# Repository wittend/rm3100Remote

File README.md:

# rm3100Remote
OSHW (TAPR License) remote magnetometer support board design

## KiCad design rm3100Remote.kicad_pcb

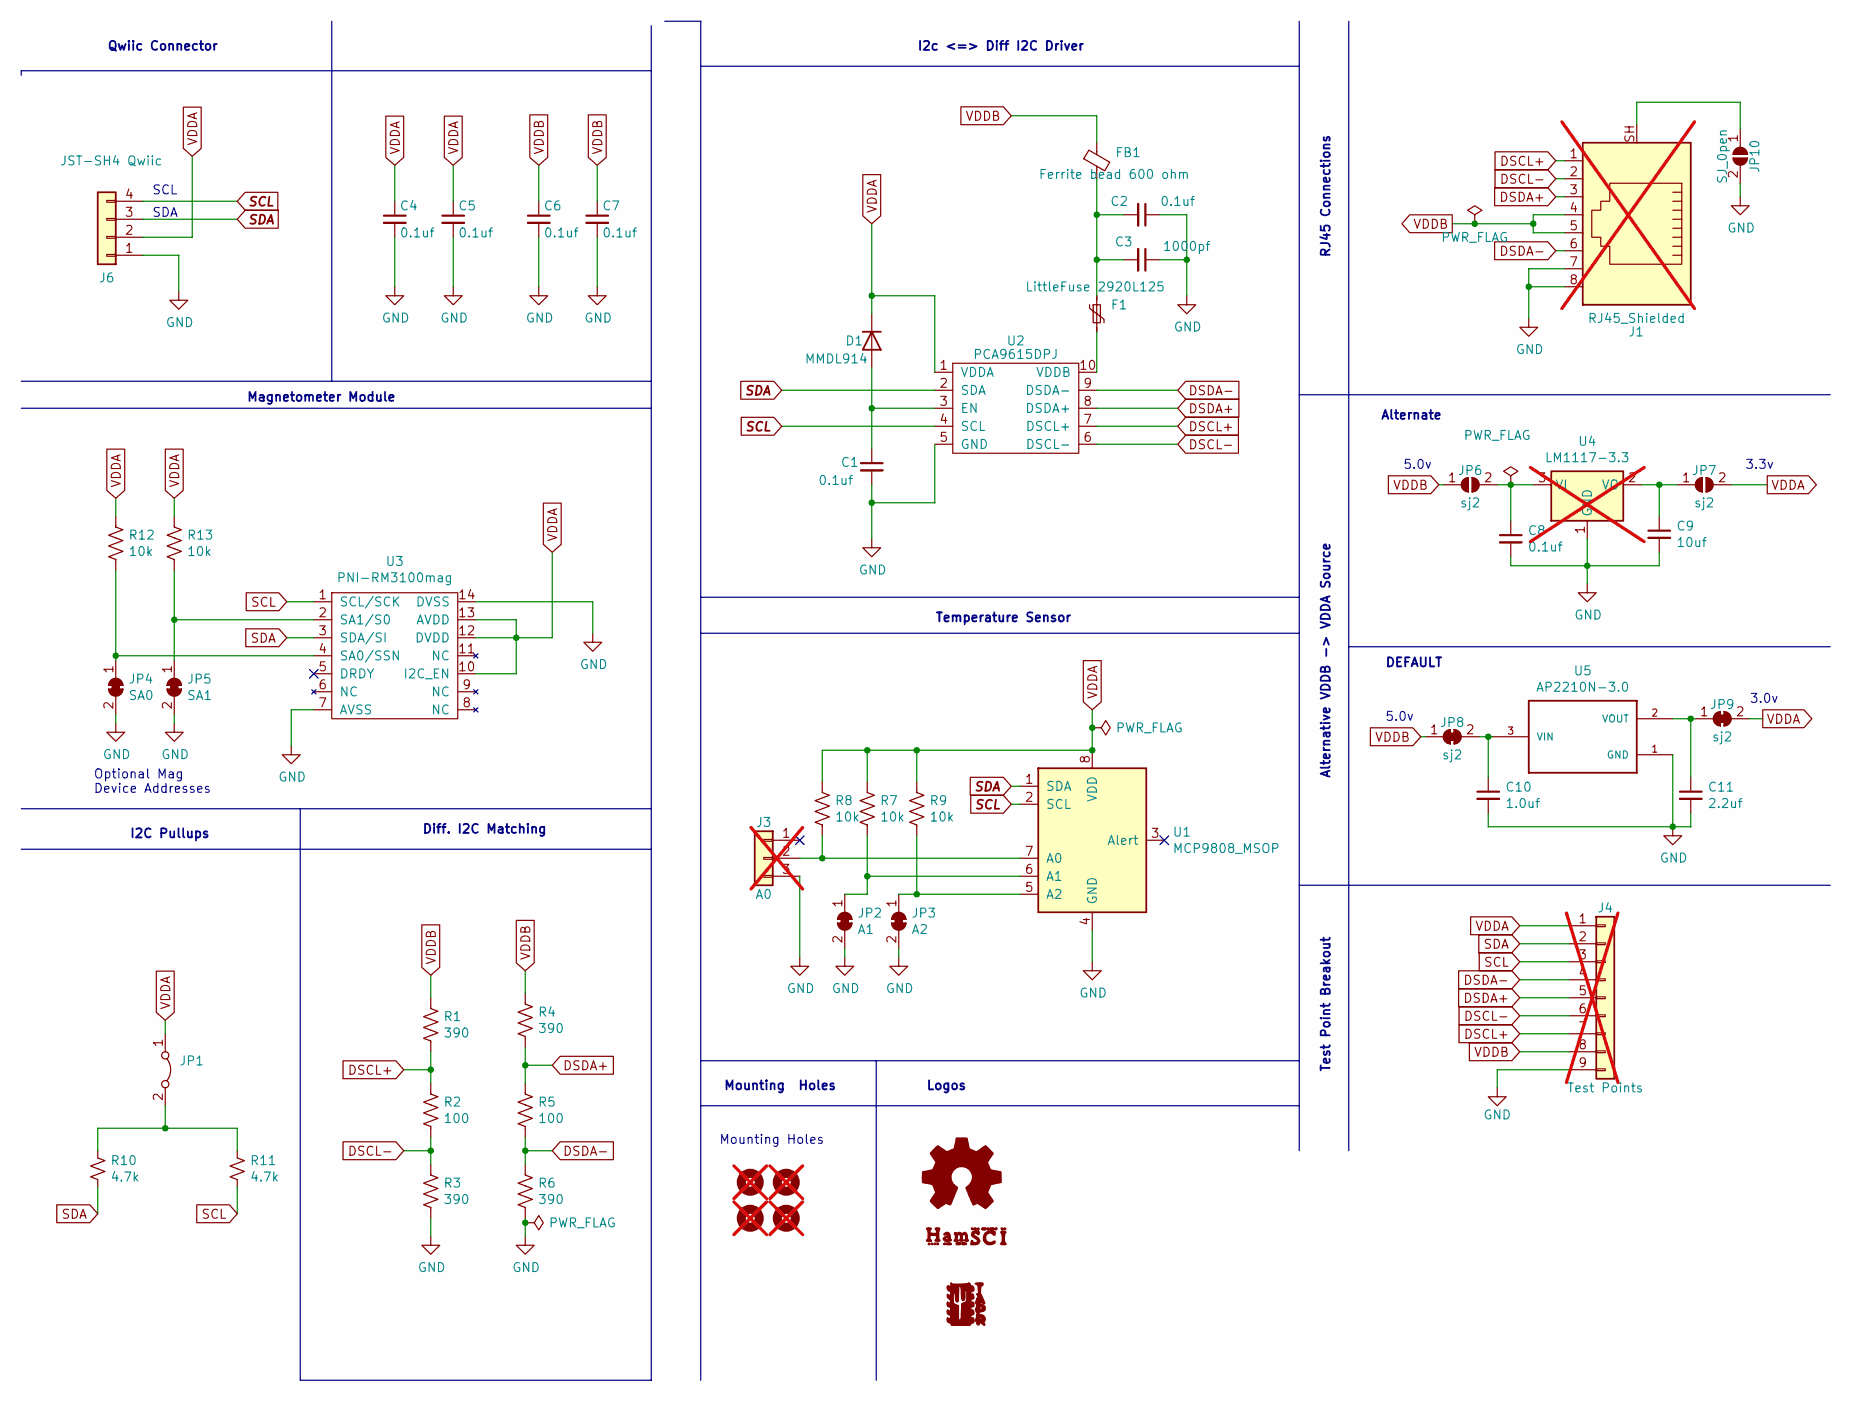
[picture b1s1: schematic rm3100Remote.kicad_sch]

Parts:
C1, C2, C4, C5, C6, C7, C8: 0.1uf; C_0603_1608Metric; LCSC C913909
C3: 1000pf; C_0603_1608Metric
C9: 10uf; C_0603_1608Metric; LCSC C182375
C10: 1.0uf; C_0603_1608Metric; LCSC C525329
C11: 2.2uf; C_0603_1608Metric; LCSC C2835569
D1: MMDL914; D_SOD-523; LCSC C2910101
F1: LittleFuse 2920L125; Fuse_0805_2012Metric; LCSC C192524
FB1: Ferrite bead 600 ohm; 0603; LCSC C79865
J1: RJ45_Shielded; RJ45_Amphenol_RJHSE5380; not fitted
J3: A0; PinHeader_1x03_P2.54mm_Vertical; not fitted
J4: Test Points; PinHeader_1x09_P2.54mm_Vertical; not fitted
J6: JST-SH4 Qwiic; JST_SH_SM04B-SRSS-TB_1x04-1MP_P1.00mm_Horizontal; LCSC C5223639
JP1: Jumper_2_Bridged; SolderJumper-2_P1.3mm_Bridged_RoundedPad1.0x1.5mm
JP2: A1; SolderJumper-2_P1.3mm_Bridged_RoundedPad1.0x1.5mm
JP3: A2; SolderJumper-2_P1.3mm_Bridged_RoundedPad1.0x1.5mm
JP4: SA0; SolderJumper-2_P1.3mm_Bridged_RoundedPad1.0x1.5mm
JP5: SA1; SolderJumper-2_P1.3mm_Bridged_RoundedPad1.0x1.5mm
JP6, JP7: sj2; SolderJumper-2_P1.3mm_Open_RoundedPad1.0x1.5mm
JP8, JP9: sj2; SolderJumper-2_P1.3mm_Bridged_RoundedPad1.0x1.5mm
JP10: SJ_0pen; SolderJumper-2_P1.3mm_Open_RoundedPad1.0x1.5mm
MK1, MK2, MK3, MK4: M2.5; MountingHole_2.7mm_M2.5; not fitted
R1, R3, R4, R6: 390; R_0603_1608Metric; LCSC C2907159
R2, R5: 100; R_0603_1608Metric; LCSC C2838670
R7, R8, R9, R12, R13: 10k; R_0603_1608Metric; LCSC C25804
R10, R11: 4.7k; R_0603_1608Metric; LCSC C304485
U1: MCP9808_MSOP; MSOP-8_3x3mm_P0.65mm; LCSC C94847
U2: PCA9615DPJ; TSSOP-10_3x3mm_P0.5mm; LCSC C2652385
U3: PNI-RM3100mag; PinSocket_PNI_RM3100
U4: LM1117-3.3; SOT-223-3_TabPin2; not fitted
U5: AP2210N-3.0; SOT95P280X145-3N; LCSC C500771

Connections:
DSCL+: J1.1, J4.7, R1.2, R2.1, U2.7 (DSCL+)
DSCL-: J1.2, J4.6, R2.2, R3.1, U2.6 (DSCL-)
DSDA+: J1.3, J4.5, R4.2, R5.1, U2.8 (DSDA+)
DSDA-: J1.6, J4.4, R5.2, R6.1, U2.9 (DSDA-)
GND: C1.2, C2.1, C3.1, C4.2, C5.2, C6.2, C7.2, C8.2, C9.2, C10.2, C11.2, J1.7, J1.8, J3.3, J4.9, J6.1, JP2.2 (B), JP3.2 (B), JP4.2 (B), JP5.2 (B), JP10.2 (B), R3.2, R6.2, U1.4 (GND), U2.5 (GND), U3.7 (AVSS), U3.14 (DVSS), U4.1 (GND), U5.1 (GND)
unnamed: C2.2, C3.2, F1.1, FB1.2
unnamed: C1.1, D1.2 (A), U2.3 (EN)
unnamed: J3.2, R8.2, U1.7 (A0)
unnamed: JP1.2 (B), R10.1, R11.1
unnamed: JP2.1 (A), R7.2, U1.6 (A1)
unnamed: JP3.1 (A), R9.2, U1.5 (A2)
unnamed: JP4.1 (A), R12.2, U3.4 (SA0/SSN)
unnamed: JP5.1 (A), R13.2, U3.2 (SA1/S0)
unnamed: C8.1, JP6.2 (B), U4.3 (VI)
unnamed: C9.1, JP7.1 (A), U4.2 (VO)
unnamed: C10.1, JP8.2 (B), U5.3 (VIN)
unnamed: C11.1, JP9.1 (A), U5.2 (VOUT)
unnamed: J1.SH, JP10.1 (A)
unnamed: F1.2, U2.10 (VDDB)
SCL: J4.3, J6.4, R11.2, U1.2 (SCL), U2.4 (SCL), U3.1 (SCL/SCK)
SDA: J4.2, J6.3, R10.2, U1.1 (SDA), U2.2 (SDA), U3.3 (SDA/SI)
VDDA: C4.1, C5.1, D1.1 (K), J4.1, J6.2, JP1.1 (A), JP7.2 (B), JP9.2 (B), R7.1, R8.1, R9.1, R12.1, R13.1, U1.8 (VDD), U2.1 (VDDA), U3.10 (I2C_EN), U3.12 (DVDD), U3.13 (AVDD)
VDDB: C6.1, C7.1, FB1.1, J1.4, J1.5, J4.8, JP6.1 (A), JP8.1 (A), R1.1, R4.1

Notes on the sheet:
Mounting Holes
Optional Mag Device Addresses
Diff. I2C Matching
Alternative VDDB -> VDDA Source
Temperature Sensor
SDA
Alternate
DEFAULT
RJ45 Connections
SCL
Mounting Holes
3.3v
5.0v
I2c <=> Diff I2C Driver
I2C Pullups
3.0v
Magnetometer Module
Qwiic Connector
Test Point Breakout
Logos

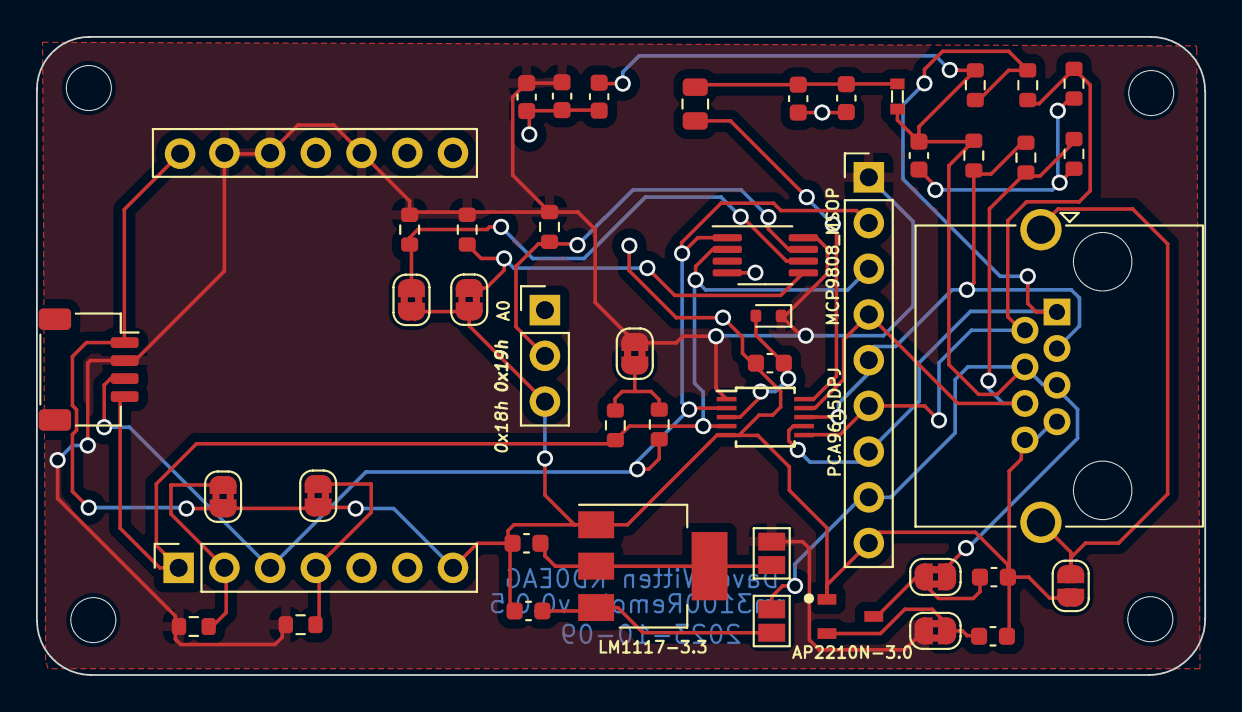
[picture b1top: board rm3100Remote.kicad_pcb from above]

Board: 2 copper layers, 64.9 x 35.5 mm, 51 parts (1 on the bottom side), 23 nets.

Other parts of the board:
TAPR Logo: TAPR; tapr_logo_bSilk_transp_10x12

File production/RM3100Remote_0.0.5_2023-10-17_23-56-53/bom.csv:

Designator,Footprint,Quantity,Value,LCSC Part #
"C1, C2, C4, C5, C6, C7, C8",0603,7,0.1uf,C913909
C10,0603,1,1.0uf,C525329
C11,0603,1,2.2uf,C2835569
C3,0603,1,1000pf,C1856398
C9,0603,1,10uf,C182375
D1,0603,1,1N4148,C2910101
F1,0805,1,LittleFuse  2920L125,C192524
FB1,0805,1,Ferrite,C79865
J3,PinHeader_1x03_P2.54mm_Vertical,1,A0,DNP
J4,PinHeader_1x09_P2.54mm_Vertical,1,Test Points,DNP
J6,JST_SH_SM04B-SRSS-TB_1x04-1MP_P1.00mm_Horizontal,1,JST-SH4 Qwiic,C5223639
JP1,SolderJumper-2_P1.3mm_Bridged2Bar_RoundedPad1.0x1.5mm,1,Jumper_2_Bridged,
JP10,SolderJumper-2_P1.3mm_Open_RoundedPad1.0x1.5mm,1,SJ_0pen,
JP2,SolderJumper-2_P1.3mm_Bridged2Bar_RoundedPad1.0x1.5mm,1,A1,
JP3,SolderJumper-2_P1.3mm_Bridged2Bar_RoundedPad1.0x1.5mm,1,A2,
JP4,SolderJumper-2_P1.3mm_Bridged2Bar_RoundedPad1.0x1.5mm,1,SA0,
JP5,SolderJumper-2_P1.3mm_Bridged2Bar_RoundedPad1.0x1.5mm,1,SA1,
"JP6, JP7",SolderJumper-2_P1.3mm_Open_Pad1.0x1.5mm,2,sj2,
"JP8, JP9",SolderJumper-2_P1.3mm_Bridged2Bar_RoundedPad1.0x1.5mm,2,sj2,
"R1, R3, R4, R6",0603,4,390,C2907159
"R10, R11",0603,2,4.7k,C304485
"R12, R13, R7, R8, R9",0603,5,10k,C25804
"R2, R5",0603,2,100,C2838670
U1,MSOP-8_3x3mm_P0.65mm,1,MCP9808_MSOP,C94847
U2,TSSOP-10_3x3mm_P0.5mm,1,PCA9615DPJ,C2652385
U3,PinSocket_PNI_RM3100,1,PNI-RM3100mag,
U5,SOT95P280X145-3N,1,AP2210N-3.0,C500771
